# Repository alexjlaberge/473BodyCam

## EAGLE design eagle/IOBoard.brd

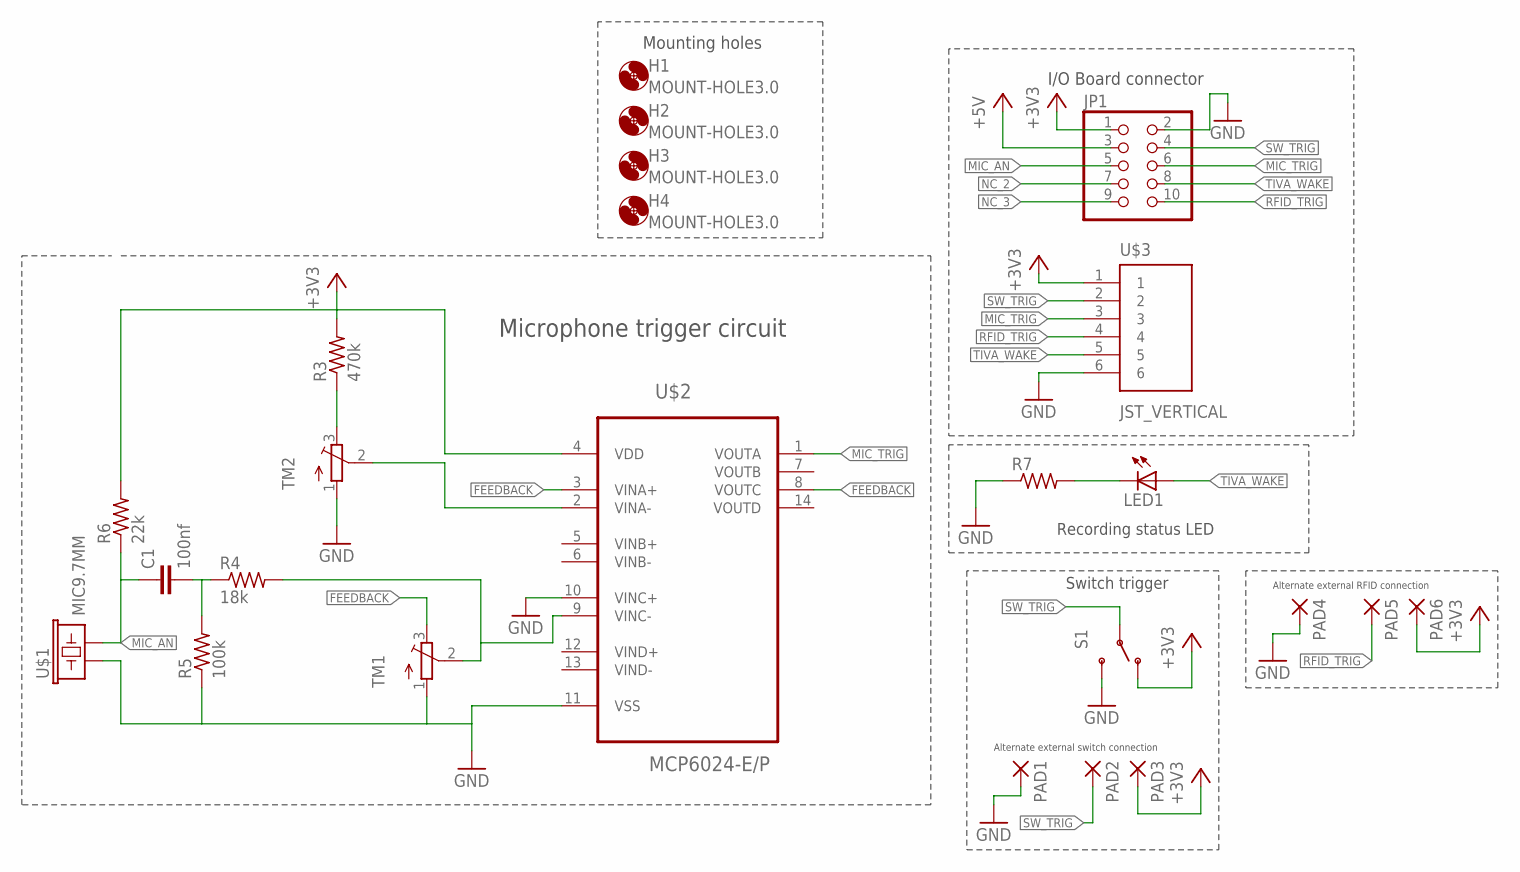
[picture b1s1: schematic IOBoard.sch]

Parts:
C1: 100nf; C0603
H1, H2, H3, H4: MOUNT-HOLE3.0; 3,0
JP1: PINHD-2X5; 2X05
LED1: LED10MM
PAD1, PAD2, PAD3, PAD4, PAD5, PAD6: 2,54/1,0
R3: 470k; R0603
R4: 18k; R0603
R5: 100k; R0603
R6: 22k; R0603
R7: R-US_R0603; R0603
S1: SWITCH-SPDTPTH; SWITCH-SPDT
TM1, TM2: TRIMPOTTC33X; TC33X
U$1: MIC9.7MM; MIC-9.7MM
U$2: MCP6024-E/P; DIP254P762X533-14
U$3: JST_VERTICAL; JST-6-SMD-VERT-1.0MM

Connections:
+3V3: JP1.1, PAD3.1, PAD6.1, R3.2, R6.2, S1.1 (O), U$2.4 (VDD), U$3.1
+5V: JP1.3
FEEDBACK: TM1.3 (E), U$2.3 (VINA+), U$2.8 (VOUTC)
GND: JP1.2, PAD1.1, PAD4.1, R5.1, R7.1, S1.3 (S), TM1.1 (A), TM2.1 (A), U$1.1, U$2.10 (VINC+), U$2.11 (VSS), U$3.6
MIC_AN: C1.1, JP1.5, R6.1, U$1.2
MIC_TRIG: JP1.6, U$2.1 (VOUTA), U$3.3
unnamed: R4.2, TM1.2 (S), U$2.9 (VINC-)
unnamed: TM2.2 (S), U$2.2 (VINA-)
unnamed: R3.1, TM2.3 (E)
unnamed: LED1.K (C), R7.2
unnamed: C1.2, R4.1, R5.2
NC_2: JP1.7
NC_3: JP1.9
RFID_TRIG: JP1.10, PAD5.1, U$3.4
SW_TRIG: JP1.4, PAD2.1, S1.2, U$3.2
TIVA_WAKE: JP1.8, LED1.A, U$3.5

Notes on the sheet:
I/O Board connector
Switch trigger
Recording status LED
Microphone trigger circuit
Alternate external switch connection
Mounting holes
Alternate external RFID connection

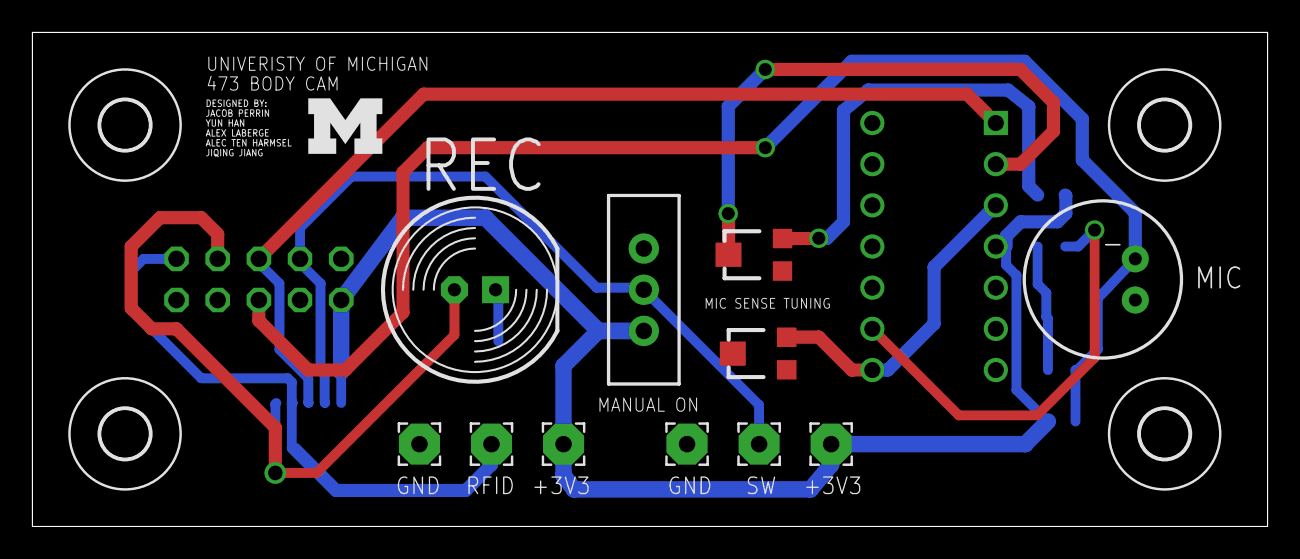
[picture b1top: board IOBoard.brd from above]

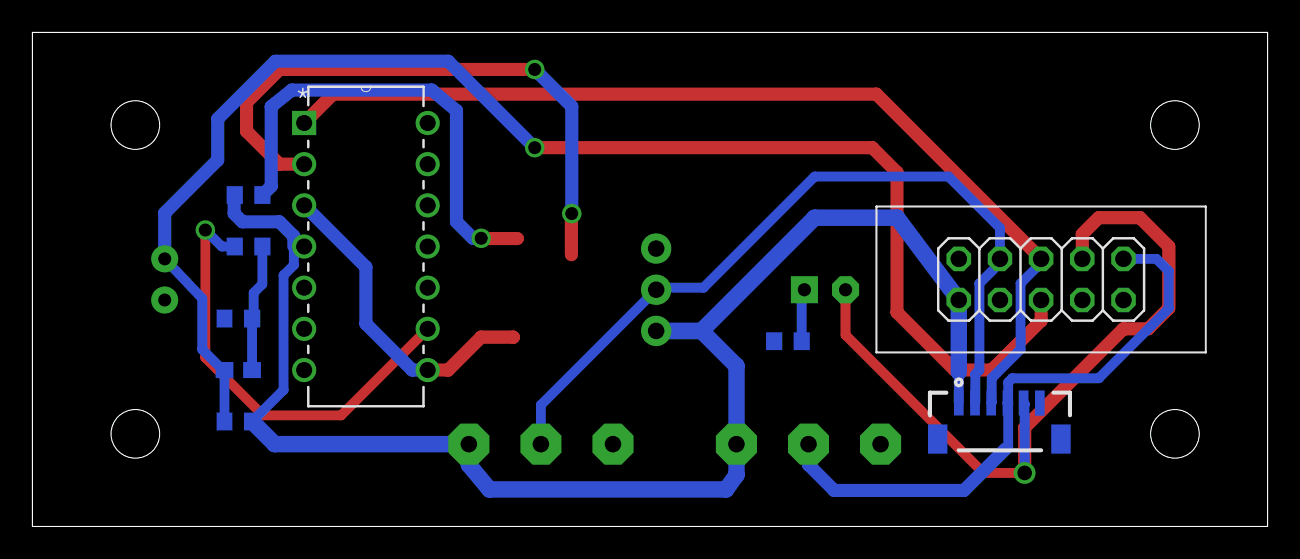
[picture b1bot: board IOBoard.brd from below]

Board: 2 copper layers, 76.2 x 30.5 mm, 25 parts (9 on the bottom side), 13 nets.

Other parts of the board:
U$4: BLOCK-M-5MM

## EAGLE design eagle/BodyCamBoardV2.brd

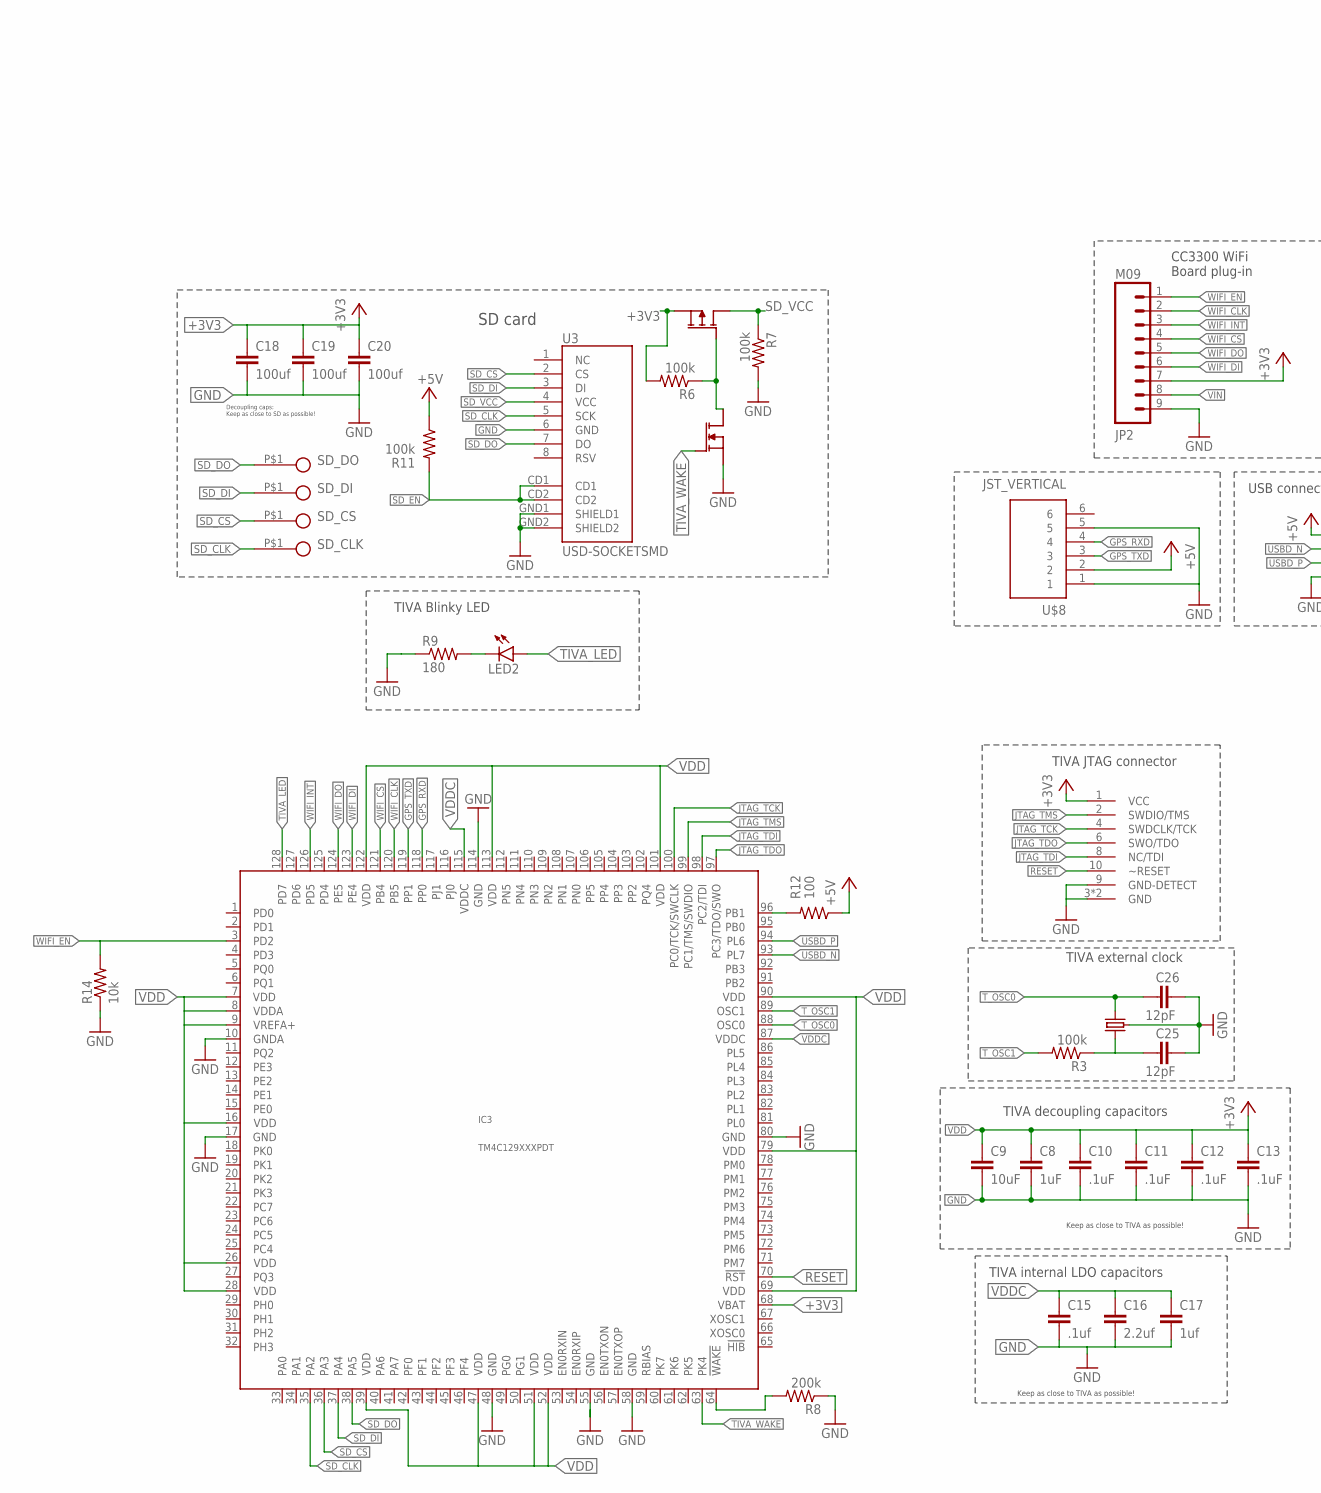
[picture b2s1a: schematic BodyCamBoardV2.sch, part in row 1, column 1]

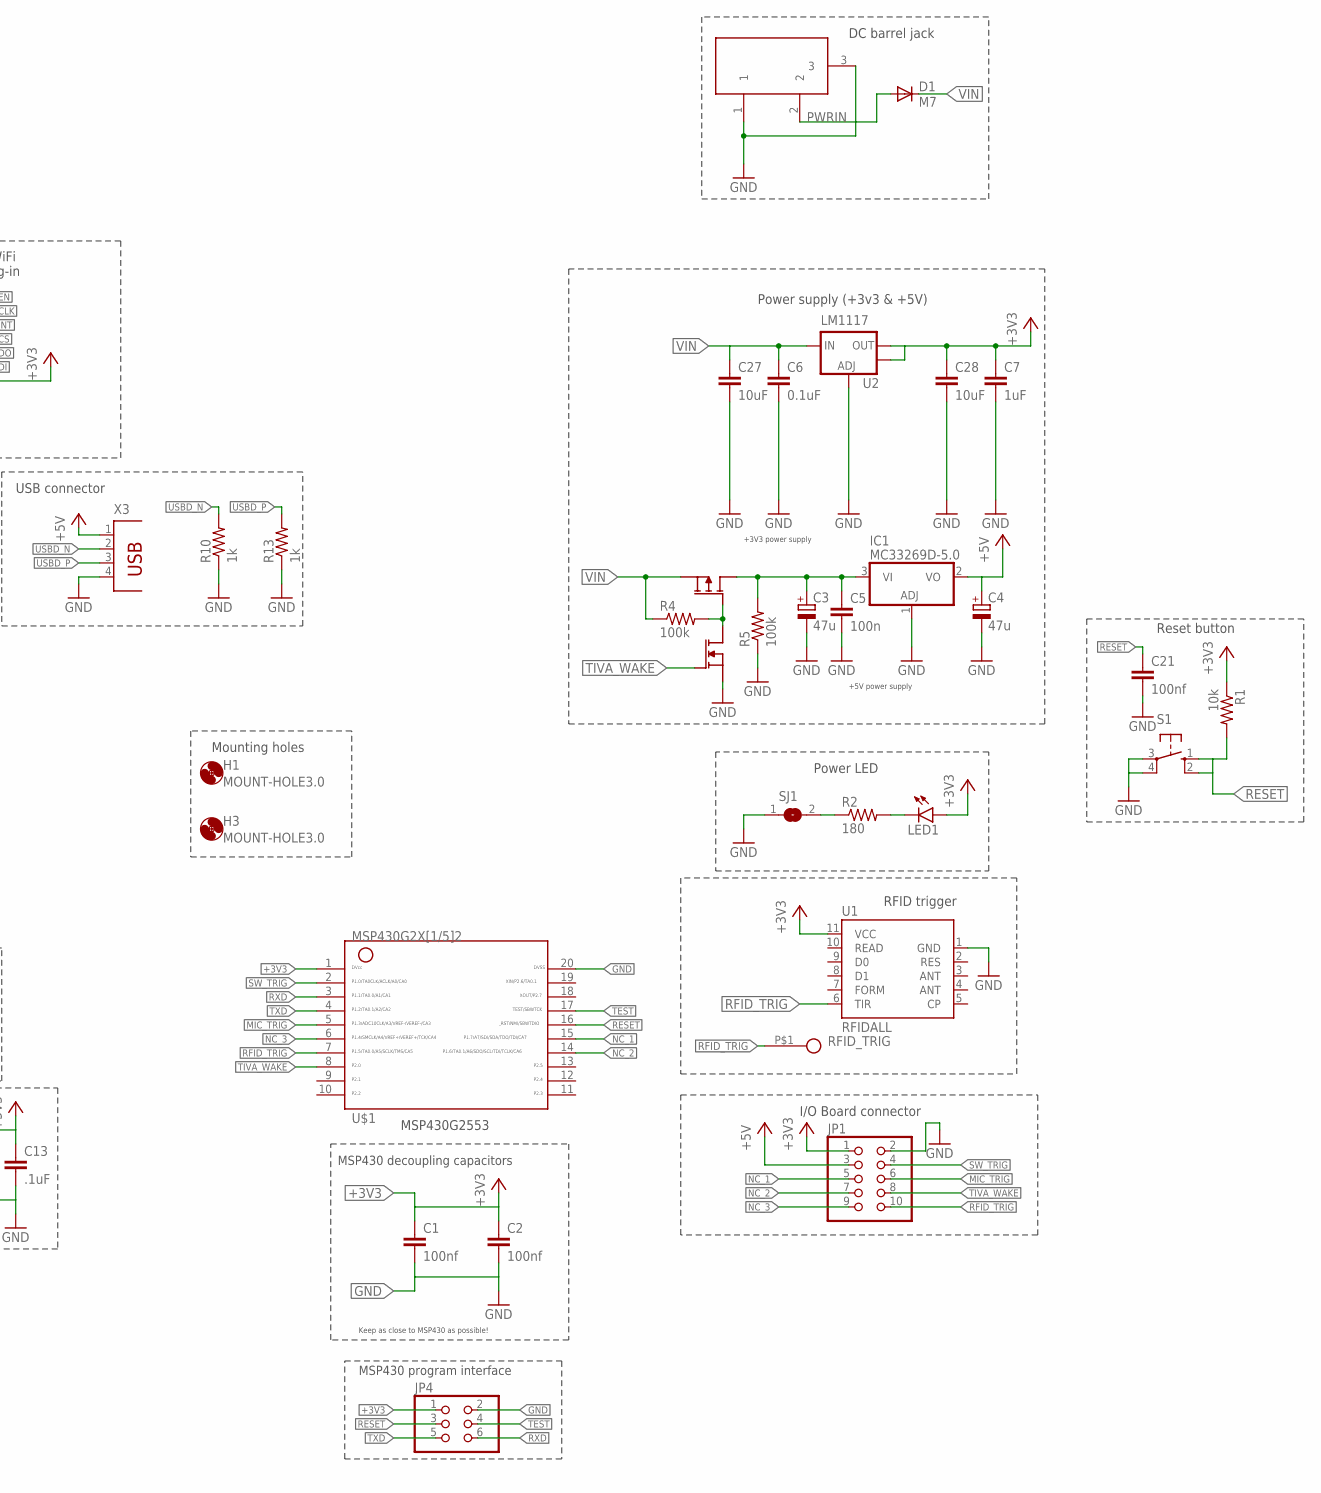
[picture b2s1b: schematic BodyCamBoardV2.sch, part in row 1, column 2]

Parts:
C1, C2, C21: 100nf; C0603
C3, C4: 47u; PANASONIC_D
C5: 100n; C0603
C6: 0.1uF; 0603-CAP
C7: 1uF; 0603-CAP
C8: 1uF; C0805
C9: 10uF; C0805
C10, C11, C12, C13: .1uF; C0603
C15: .1uf; C0805
C16: 2.2uf; C0805
C17: 1uf; C0805
C18, C19, C20: 100uf; C1206
C25, C26: 12pF; C0402
C27, C28: 10uF; 0603-CAP
D1: M7; SMB
H1, H3: MOUNT-HOLE3.0; 3,0
IC1: MC33269D-5.0; DPACK
IC3: TM4C129XXXPDT; PDT_S-PQFP-G128
JP1: PINHD-2X5; 2X05
JP2: M09; 1X09
JP4: PINHD-2X3; 2X03
LED1, LED2: LED0603; LED-0603@1
R1, R14: 10k; R0603
R2, R9: 180; R0603
R3: 100k; R0402
R4, R5, R6, R7: 100k; R0603
R8: 200k; R0603
R10, R13: 1k; R0402
R11: 100k; 0603-RES
R12: 100; 0603-RES
RFID_TRIG: TEST_POINTSMD_MINI; TEST_SMD_MINI_5019
S1: 10-XX; B3F-10XX
SD_CLK: TEST_POINTSMD_MINI; TEST_SMD_MINI_5019
SD_CS: TEST_POINTSMD_MINI; TEST_SMD_MINI_5019
SD_DI: TEST_POINTSMD_MINI; TEST_SMD_MINI_5019
SD_DO: TEST_POINTSMD_MINI; TEST_SMD_MINI_5019
SJ1: SJ
U1: RFIDALL; ID_PACKAGE
U2: LM1117; SOT223
U3: USD-SOCKETSMD; MICRO-SD-SOCKET-PP
U$1: G2X[1/5]2---PW20; PW20
U$2, U$5: STR2P3LLH6; SOT-23
U$3: 25MHz; 4-SMD-SWITCH
U$4, U$6: IRLML2402TRPBF; SOT-23
U$7: 2X5_0.05"_CORTEX_DEBUGTH_KEYED_UNSHROUDED; 2X5_0.05"_TH_KEYED_NS
U$8: JST_VERTICAL; JST-6-SMD-VERT-1.0MM
X2: DC21MMX; DC-21MM
X3: PN87520

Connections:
+3V3: C1.1, C2.1, C7.1, C18.1, C19.1, C20.1, C28.1, IC3.68 (VBAT), JP1.1, JP2.7, JP4.1, LED1.A, R1.1, R6.2, U1.11 (VCC), U2.2 (OUT), U2.4 (OUT), U$1.1, U$5.2 (S), U$7.1 (VCC)
+5V: C4.+, IC1.2 (VO), JP1.3, R11.1, R12.1, U$8.2, X3.1
GND: C1.2, C2.2, C3.-, C4.-, C5.2, C6.2, C7.2, C8.2, C9.2, C10.2, C11.2, C12.2, C13.2, C15.2, C16.2, C17.2, C18.2, C19.2, C20.2, C21.2, C25.2, C26.2, C27.2, C28.2, IC1.1 (ADJ), IC3.10 (GNDA), IC3.17 (GND), IC3.48 (GND), IC3.55 (GND), IC3.58 (GND), IC3.80 (GND), IC3.114 (GND), JP1.2, JP2.9, JP4.2, R5.1, R7.2, R8.1, R10.1, R13.1, R14.1, S1.3, S1.4 (P1), SJ1.1, U1.1 (GND), U2.1 (ADJ), U3.6 (GND), U3.GND1 (SHIELD1), U3.GND2 (SHIELD2), U$1.20, U$3.2 (GND), U$3.4 (GND), U$4.2 (S), U$6.2 (S), U$7.3 (GND), U$7.5 (GND), U$7.9 (GND-DETECT), U$8.1, U$8.5, X2.1, X2.3, X3.4
GPS_RXD: IC3.118 (PP0), U$8.4
GPS_TXD: IC3.119 (PP1), U$8.3
JTAG_TCK: IC3.100 (PC0/TCK/SWCLK), U$7.4 (SWDCLK/TCK)
JTAG_TDI: IC3.98 (PC2/TDI), U$7.8 (NC/TDI)
JTAG_TDO: IC3.97 (PC3/TDO/SWO), U$7.6 (SWO/TDO)
JTAG_TMS: IC3.99 (PC1/TMS/SWDIO), U$7.2 (SWDIO/TMS)
MIC_TRIG: JP1.6, U$1.5
unnamed: LED1.C, R2.2
unnamed: R2.1, SJ1.2
unnamed: LED2.C, R9.2
unnamed: R4.2, U$2.1 (G), U$4.3 (D)
unnamed: C3.+, C5.1, IC1.3 (VI), R5.2, U$2.3 (D)
unnamed: R6.1, U$5.1 (G), U$6.3 (D)
unnamed: IC3.96 (PB1), R12.2
NC_1: JP1.5, U$1.15
NC_2: JP1.7, U$1.14
NC_3: JP1.9, U$1.6
PWRIN: D1.A, X2.2
RESET: C21.1, IC3.70 (!RST), JP4.3, R1.2, S1.1 (S), S1.2 (S1), U$1.16, U$7.10 (~RESET)
RFID_TRIG: JP1.10, RFID_TRIG.P$1, U1.6 (TIR), U$1.7
RXD: JP4.6, U$1.3
SD_CLK: IC3.35 (PA2), SD_CLK.P$1, U3.5 (SCK)
SD_CS: IC3.36 (PA3), SD_CS.P$1, U3.2 (CS)
SD_DI: IC3.37 (PA4), SD_DI.P$1, U3.3 (DI)
SD_DO: IC3.38 (PA5), SD_DO.P$1, U3.7 (DO)
SD_EN: R11.2, U3.CD1, U3.CD2
SD_VCC: R7.1, U3.4 (VCC), U$5.3 (D)
SW_TRIG: JP1.4, U$1.2
TEST: JP4.4, U$1.17
TIVA_LED: IC3.128 (PD7), LED2.A
TIVA_WAKE: IC3.63 (PK4), JP1.8, U$1.8, U$4.1 (G), U$6.1 (G)
TXD: JP4.5, U$1.4
T_OSC0: C26.1, IC3.88 (OSC0), U$3.3 (2)
T_OSC1: C25.1, IC3.89 (OSC1), R3.1, U$3.1
USBD_N: IC3.93 (PL7), R10.2, X3.2
USBD_P: IC3.94 (PL6), R13.2, X3.3
VDD: C8.1, C9.1, C10.1, C11.1, C12.1, C13.1, IC3.7 (VDD), IC3.8 (VDDA), IC3.9 (VREFA+), IC3.16 (VDD), IC3.26 (VDD), IC3.28 (VDD), IC3.39 (VDD), IC3.47 (VDD), IC3.51 (VDD), IC3.52 (VDD), IC3.69 (VDD), IC3.79 (VDD), IC3.90 (VDD), IC3.101 (VDD), IC3.113 (VDD), IC3.122 (VDD)
VDDC: C15.1, C16.1, C17.1, IC3.87 (VDDC), IC3.115 (VDDC)
VIN: C6.1, C27.1, D1.C, JP2.8, R4.1, U2.3 (IN), U$2.2 (S)
WAKE_SIG: IC3.64 (!WAKE), R8.2
WIFI_CLK: IC3.120 (PB5), JP2.2
WIFI_CS: IC3.121 (PB4), JP2.4
WIFI_DI: IC3.123 (PE4), JP2.6
WIFI_DO: IC3.124 (PE5), JP2.5
WIFI_EN: IC3.3 (PD2), JP2.1, R14.2
WIFI_INT: IC3.126 (PD5), JP2.3

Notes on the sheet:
MSP430 decoupling capacitors
Reset button
Power LED
Keep as close to MSP430 as possible!
MSP430G2553
RFID trigger
Power supply (+3v3 & +5V)
+5V power supply
USB connector
TIVA decoupling capacitors
Keep as close to TIVA as possible!
TIVA internal LDO capacitors
I/O Board connector
Decoupling caps: Keep as close to SD as possible!
TIVA JTAG connector
DC barrel jack
MSP430 program interface
TIVA external clock
+3V3 power supply
CC3300 WiFi Board plug-in
TIVA Blinky LED
Mounting holes
SD card

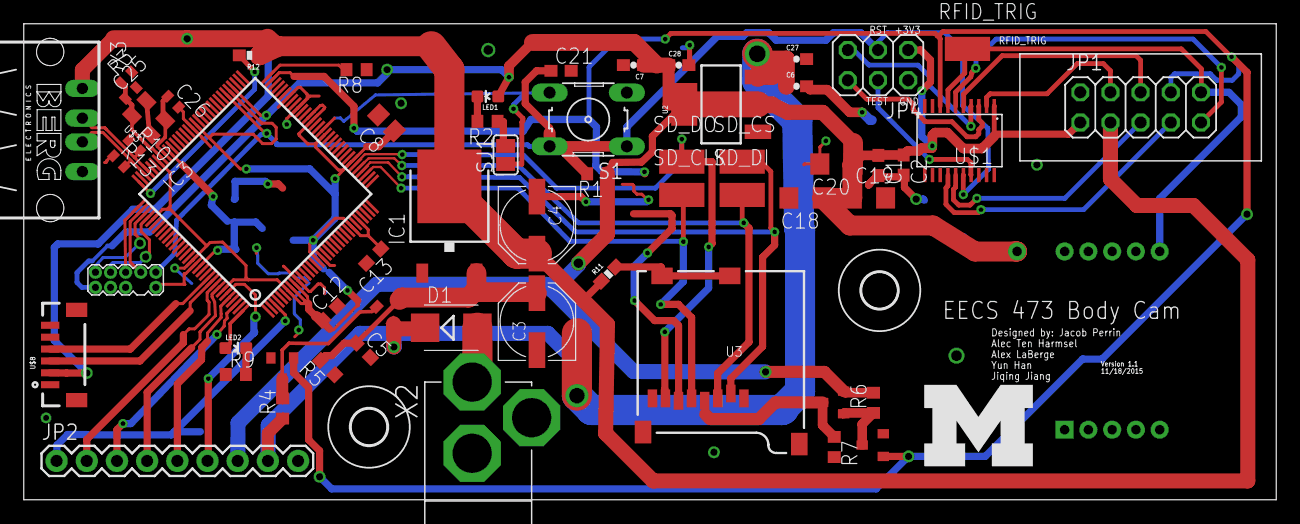
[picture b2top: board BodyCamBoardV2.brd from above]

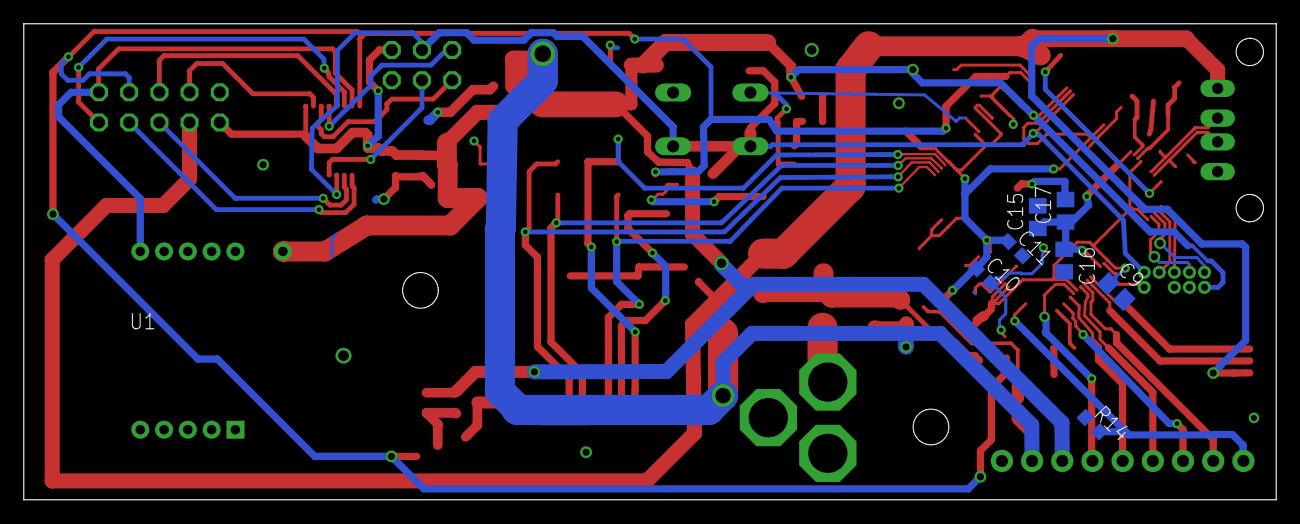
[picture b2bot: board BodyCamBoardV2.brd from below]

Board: 2 copper layers, 105.4 x 40.1 mm, 69 parts (8 on the bottom side), 49 nets.

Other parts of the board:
U$9: BLOCK-M-10MM

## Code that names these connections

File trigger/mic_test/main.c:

#include <msp430.h> 

#define SW_TRIG BIT0 //p1.0
#define MIC_TRIG BIT3 //p1.3
#define RFID_TRIG BIT5 //p1.5
#define TIVA_WAKE BIT0 //p2.0

//1 second = 1 tick
#define RFID_timeout 300 // 5 minutes
#define MIC_timeout 10 // 10 seconds

volatile unsigned int SW_ON = 0;
volatile unsigned int MIC_ON = 0;
volatile unsigned int RFID_ON = 0;

volatile unsigned int RFID_time = 0;
volatile unsigned int MIC_time = 0;

void config()
{
	// Configure Timer Interrupt
	WDTCTL = WDTPW + WDTHOLD; 							// Stop watchdog timer
	TACCTL0 |= CCIE; // enable CCRO interrupt
	//TACCR0 = 32768-1;
	TACCR0 = 5300;
	TACTL |= TASSEL_1 + MC_1; // ACLK, upmode

	BCSCTL3 |= LFXT1S_2;		// Basic Clock System Control.

	// Configure GPIO
	P2DIR |= (TIVA_WAKE);
	P2OUT &= ~(TIVA_WAKE);

	P2DIR |= (BIT2);
	P2OUT &= ~(BIT2);

	// Configure GPIO Interrupt
	P1IE |= (SW_TRIG + MIC_TRIG + RFID_TRIG);						// Port 1 interrupt enabled for SW_TRIGitch
	P1IES &= ~(SW_TRIG + MIC_TRIG + ~RFID_TRIG); 						// Interrupt edge set Bit0 = low to high, Bit1 = high to low
	P1IFG &= ~(SW_TRIG + MIC_TRIG + RFID_TRIG); 						// Clear interrupt flag
	__enable_interrupt(); // enable all interrupts
}


void update()
{
	if(SW_ON || MIC_ON || RFID_ON)
		P2OUT |= TIVA_WAKE;
	else
		P2OUT &= ~TIVA_WAKE;
}

int main(void)
{
	config();

	while(1)
	{
		_bis_SR_register(LPM3_bits + GIE); //Enter Low Power Mode 3 with interrupts
	}

}
#pragma vector=TIMER0_A0_VECTOR
__interrupt void Timer_A (void)
{
	P2OUT ^= BIT2;
	if (RFID_ON){
		if(RFID_time == RFID_timeout) {
			RFID_time = 0;
			RFID_ON = 0;
			update();
		}
		else {
			RFID_time++;
		}
	}
	if (MIC_ON){
		if(MIC_time >= MIC_timeout) {
			MIC_time = 0; // reset count
			MIC_ON = 0; // turn flag off
			update();
		}
		else {
			MIC_time++;
		}
	}
	else {
		MIC_time = 0;
		update();
	}
}

// Port 1 interrupt service routine
#pragma vector=PORT1_VECTOR
__interrupt void Port_1(void)
{
	// Switch Triggered
	if((P1IFG & SW_TRIG) == SW_TRIG)
	{
		P1IES ^= SW_TRIG; 						// Toggle interrupt edge for SW_TRIGitch
		P1IFG &= ~SW_TRIG;						// Clear interrupt flag
		SW_ON = 0;
		if((P1IN & SW_TRIG) == SW_TRIG) {
			SW_ON = 1;
		}
	}
	// Mic Triggered
	if ((P1IFG & MIC_TRIG) == MIC_TRIG)
	{

		MIC_ON = 1;

		P1IFG &= ~MIC_TRIG;
	}
	// RFID Triggered
	if ((P1IFG & RFID_TRIG) == RFID_TRIG)
	{
		P1IES ^= RFID_TRIG;
		P1IFG &= ~RFID_TRIG;
		if((P1IN & RFID_TRIG) == RFID_TRIG) {
			RFID_ON = 0;
		}
		else
			RFID_ON = 1;
		P1IFG &= ~RFID_TRIG;
	}
	update();
}

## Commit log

2015-10-08 Start proposal
2015-10-08 Finish proposal
2015-10-25 Add initial circuit schematic
2015-10-25 Start some UVC stuff
2015-10-25 Add code to respond to USB events
2015-10-25 Update cproject, disable sys tick interrupt
2015-10-25 configure pins
2015-10-25 Add more USB code
2015-10-28 Add some LED code
2015-10-28 Add include dir to CCS project
2015-10-28 Add gitignore for video code
2015-10-30 Replace USB interrupt handler with host variant.
    This should be slightly more efficient than
    using the OTG interrupt.
2015-10-30 Switch from OTG to HCD
2015-10-31 Increase memory pool size, misc cleanup
2015-11-01 Initial implementation of uvc_open
2015-11-04 Start documenting uvc header
2015-11-04 Set up endpoints
2015-11-04 20151103spi
    example code
2015-11-04 Add some defines, misc functions. uvc_open done.
    uvc_open now opens and sets up the interrupt endpoint if it is available,
    which is all that it probably should do. Configuring the video device
    further can be done with other functions.
2015-11-04 Start work on Interface Association Descriptor
2015-11-05 Add uvc_get_config()
2015-11-05 Update main board
2015-11-05 bugfix uvc_get_config()
2015-11-06 Start some updates to uvc_get_config
2015-11-06 Add a lot of config parsing code
2015-11-07 Add more parsing code
2015-11-07 harden some parsing functions
2015-11-07 More data processing code
2015-11-07 Add extension unit descriptor processing
2015-11-08 Add video streaming interface parsing code
2015-11-09 Add some more parsing code.
    It is getting through a lot of the streaming config, but erroring after parsing
    the first stream descriptor group.
2015-11-09 USB config parsing code gets back to main loop
2015-11-09 Receiving events on the isochronous pipe
2015-11-09 Add some reading code. Does not work
2015-11-10 Add probe/commit control struct
2015-11-11 SDC
    sd card 1110
2015-11-12 Add some SET_CUR stuff
2015-11-12 Sending SET_INTERFACE, something is coming back
2015-11-12 Now reading payload header, just need to read payload
2015-11-12 Add some ACKing code, misc other stuff
2015-11-12 Add another data ACK
2015-11-14 Add probe/commit control header UVC versioning
2015-11-15 Add GET_CUR op
2015-11-15 Streaming is working
2015-11-16 Added wifi application (current prototype code)
2015-11-17 473 SDC and sdcv3
    473 SDC is version 2 using ssi 2
    sdcv3 is version 3 using ssi 1
2015-11-20 Made changes to the cc3000 wifi application
2015-11-20 Add gitignore. Remove all CCS-generated files
2015-11-20 Project now compiles and links
2015-11-20 Add external UVC API
2015-11-20 Re-add uvc_init()
2015-11-20 Massive UVC refactoring
2015-11-20 UVC: Actually call callbacks
2015-11-21 changed uvc.c to include info on parsing fault
2015-11-21 Remove .launches directory; put in .gitignore
2015-11-21 uvc: Fix null pointer to configuration bug
2015-11-21 Add UVC callbacks, remove spurious DMA table
2015-11-21 uvc: Fix a couple bugs regarding the streaming endpoint
    The refactoring introduced bugs (duh), but they are mostly fixed now.
    uvc_data_cb() is getting called regularly in the main application.
2015-11-21 Add MJPEG format/frame parsing and promotion
2015-11-21 Fix UVC includes, uncomment wifi enabling
2015-11-22 Enable wifi
2015-11-22 Got frames to go over wifi
2015-11-22 Add MJPEG support to UVC callbacks
2015-11-22 Implement uvc_start_cb, uvc_end_cb
2015-11-24 SD card Demo 151124
    Working version with SSI0
2015-11-24 Removed WiFi delay and added in a new check for start and end packets
2015-11-24 Remove binaries, add to gitignore
2015-11-25 Add constants for wifi stuff
2015-11-25 uvc: Add uncompressed frame sending
2015-11-29 port to network order was wrong and is now fixed
2015-11-29 Added base station code
2015-11-29 Made the buffer vector based so I can easily call the imdecode function
2015-11-29 everything
2015-11-30 Fuck you alec
2015-11-30 BaseStation: Remove garbage, add gitignore
2015-11-30 changed the size of the wifi message
2015-11-30 Add a packet examiner
2015-11-30 Removed unnecessary beginning delay and removed system UART support
2015-12-01 uvc: Add MJPEG packet handling
2015-12-01 BaseStation: Add packet parsing library
2015-12-01 BaseStation: Add packet testing, clean up CMake
2015-12-02 tiva: Update packet format
2015-12-02 uvc: Add color matching support, bugfix mjpeg stuff
2015-12-03 pkt: Throw exception if length is wrong.
2015-12-03 BaseStation: Add Qt GUI
    Networking functionality is implemented (not tested). Picture display is
    nearly done.
2015-12-03 BaseStation: Add some more features to examine
2015-12-03 Add to pkt_test
2015-12-04 cc3000: bugfix wifi sending bigger packets
2015-12-04 BaseStation: Add dump.cpp to dump raw data
2015-12-04 BaseStation: Do not initialize dst Mat in examine
2015-12-04 BaseStation: Add send binary for testing client
2015-12-04 BaseStation: Add displaying to client
2015-12-04 BaseStation: Remote unused global buffer
2015-12-05 BaseStation: client receiving over network
2015-12-05 Add mjpeg stuff
2015-12-05 BaseStation/examine: Add MJPEG info
2015-12-05 BaseStation: Add MJPEG displaying
2015-12-05 Added a different fatfs library
2015-12-06 tiva: Only start new image if it has been sent over wifi
2015-12-06 tiva: Fix BOOL not defined error
2015-12-06 BaseStation: Catch an exception if MJPEG decode fails
2015-12-06 BaseStation: Add SD viewer
2015-12-06 BaseStation: viewer handles jpeg parse failures
2015-12-06 Working
2015-12-07 triggering codes
2015-12-07 BaseStation: Slew of TCP fixes
2015-12-07 BaseStation: TCP socket bugfix
2015-12-07 BaseStation: Add TCP backend
2015-12-09 BaseStation: add disconnected graphic
2015-12-10 BaseStation: add saving
2015-12-10 BaseStation: Add slow wifi viewer
2015-12-12 Add logo. Add references. Add power calcs.
2015-12-12 final_report: Add more to power section
2015-12-12 tex: Add 'clean' rule to Makefile
2015-12-12 tex: Update/add to online references
2015-12-13 final_report: Turn off section numbering
2015-12-13 final_report: add DOJ to glossary
2015-12-13 final_report: add missing "Figure" in front of reference
2015-12-13 final_report: add to description, add references
2015-12-13 final_report: add PCB schematics
2015-12-13 final_report: fix schematic angles
2015-12-14 final_report: add UVC interface
2015-12-14 final_report: Write a subsection about video subsys
2015-12-14 final_report: add system description graphic
2015-12-14 final_report: add budget, not in report yet
2015-12-14 Added sd card paragraph
2015-12-14 final_report: remove a bunch of old stuff
2015-12-14 added some sections
2015-12-14 added header files
2015-12-15 final_report: fix some parenthesis-related bugs
2015-12-15 final_report: add trigger flow diagram
2015-12-15 final_report: Overview edits
2015-12-15 final_report: edits to description
2015-12-15 final_report: Add a bunch of edits
2015-12-15 final_report: Even more edits
2015-12-15 final_report: update logo, update enclosure pic
2015-12-15 final_report: fix pcb figure spacing
2015-12-15 final_report: add budget

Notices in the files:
parts and their libraries:
SparkFun-LED: Licensing: Creative Commons ShareAlike 4.0 International - https://creativecommons.org/licenses/by-sa/4.0
SparkFun-Connectors: Licensing: CC v3.0 Share-Alike You are welcome to use this library for commercial purposes.
